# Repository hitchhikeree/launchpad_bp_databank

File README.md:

DataBank LaunchPad BoosterPack
=========================

A dual SD card and SPI Flash board for logging tons of data or accessing a bunch of it.

## Project Links
- <a href="http://www.hitchhikeree.org/databank/">HitchhikerEE page</a>
- <a href="http://youtu.be/DQmhQuYcrzk">YouTube video</a>
- <a href="https://docs.google.com/folder/d/0B5HjtPsFD8u5alU0WkpRbFBrZk0/edit?usp=sharing">Design files on Google Drive</a>
- <a href="http://e2e.ti.com/group/microcontrollerprojects/m/boosterpackcontest/664831.aspx">LaunchPad BoosterPack Contest page</a>

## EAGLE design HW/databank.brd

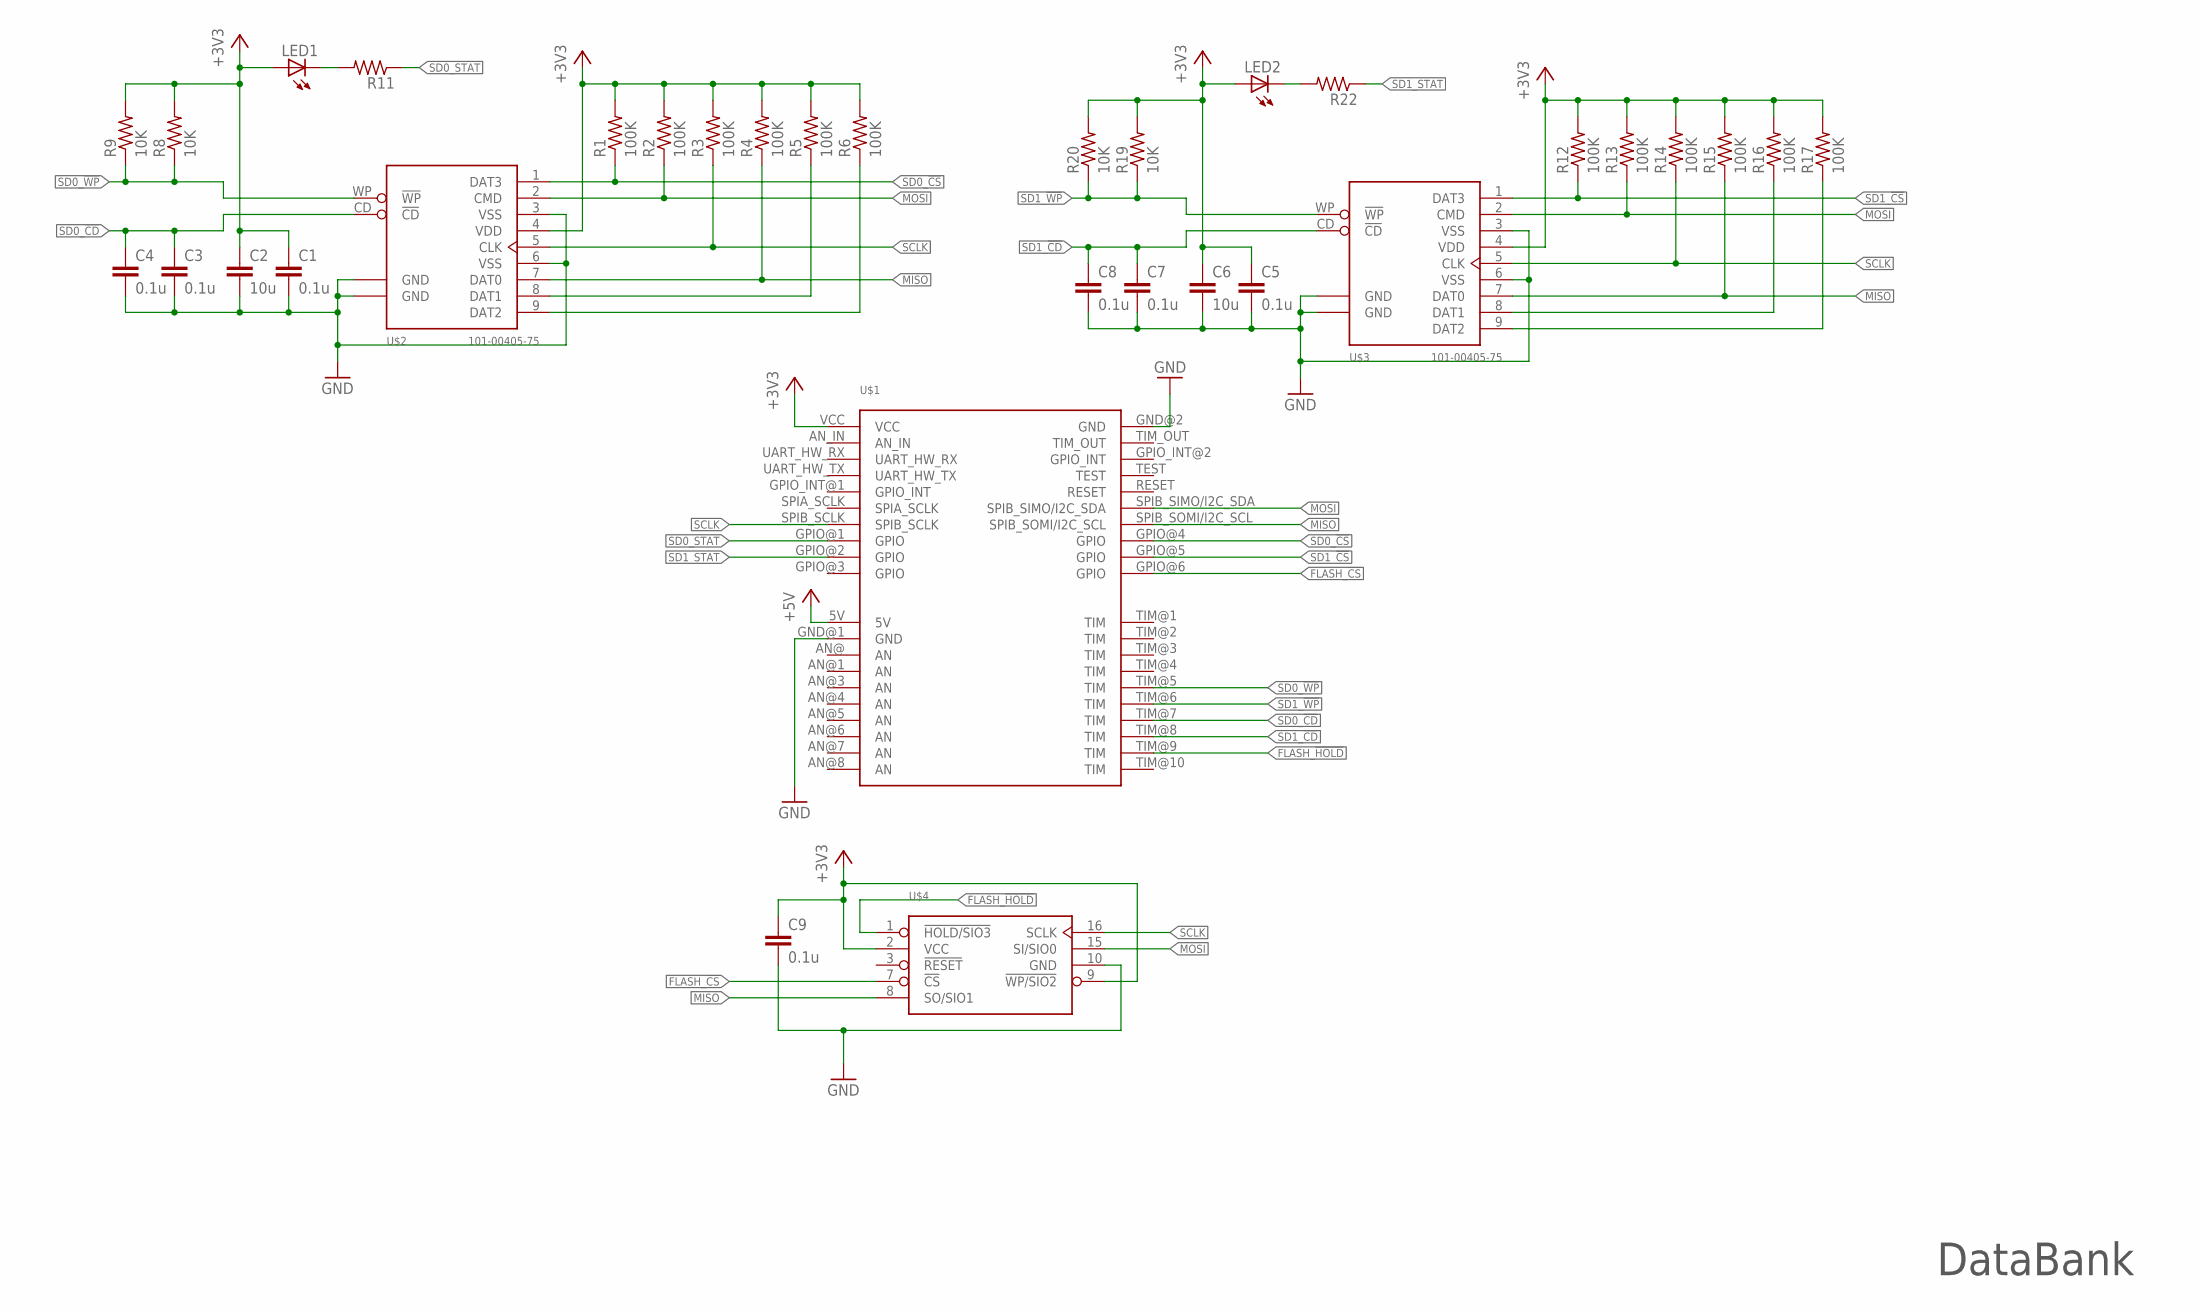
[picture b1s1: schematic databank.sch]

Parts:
C1, C3, C4, C5, C7, C8, C9: 0.1u; C0603
C2, C6: 10u; C0603
LED1, LED2: LEDCHIP-LED0603; CHIP-LED0603
R1, R2, R3, R4, R5, R6, R12, R13, R14, R15, R16, R17: 100K; R0603
R8, R9, R19, R20: 10K; R0603
R11, R22: R-US_R0603; R0603
U$1: LAUNCHPAD_BOOSTER_PACK
U$2, U$3: 101-00405-75
U$4: MX25L25635E; SO-16LD

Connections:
+3V3: C1.1, C2.1, C5.1, C6.1, C9.1, LED1.A, LED2.A, R1.2, R2.2, R3.2, R4.2, R5.2, R6.2, R8.2, R9.2, R12.2, R13.2, R14.2, R15.2, R16.2, R17.2, R19.2, R20.2, U$1.VCC, U$2.4 (VDD), U$3.4 (VDD), U$4.2 (VCC), U$4.9 (!WP/SIO2)
+5V: U$1.5V
FLASH_!CS: U$1.GPIO@6 (GPIO), U$4.7 (!CS)
FLASH_!HOLD: U$1.TIM@9 (TIM), U$4.1 (!HOLD/SIO3)
GND: C1.2, C2.2, C3.2, C4.2, C5.2, C6.2, C7.2, C8.2, C9.2, U$1.GND@1 (GND), U$1.GND@2 (GND), U$2.3 (VSS), U$2.6 (VSS), U$2.G1$GND (GND), U$2.G2$GND (GND), U$3.3 (VSS), U$3.6 (VSS), U$3.G1$GND (GND), U$3.G2$GND (GND), U$4.10 (GND)
MISO: R4.1, R15.1, U$1.SPIB_SOMI/I2C_SCL, U$2.7 (DAT0), U$3.7 (DAT0), U$4.8 (SO/SIO1)
MOSI: R2.1, R13.1, U$1.SPIB_SIMO/I2C_SDA, U$2.2 (CMD), U$3.2 (CMD), U$4.15 (SI/SIO0)
unnamed: LED1.C, R11.2
unnamed: R16.1, U$3.8 (DAT1)
unnamed: R17.1, U$3.9 (DAT2)
unnamed: R5.1, U$2.8 (DAT1)
unnamed: R6.1, U$2.9 (DAT2)
unnamed: LED2.C, R22.2
SCLK: R3.1, R14.1, U$1.SPIB_SCLK, U$2.5 (CLK), U$3.5 (CLK), U$4.16 (SCLK)
SD0_!CD: C3.1, C4.1, U$1.TIM@7 (TIM), U$2.CD (!CD)
SD0_!CS: R1.1, U$1.GPIO@4 (GPIO), U$2.1 (DAT3)
SD0_!WP: R8.1, R9.1, U$1.TIM@5 (TIM), U$2.WP (!WP)
SD0_STAT: R11.1, U$1.GPIO@1 (GPIO)
SD1_!CD: C7.1, C8.1, U$1.TIM@8 (TIM), U$3.CD (!CD)
SD1_!CS: R12.1, U$1.GPIO@5 (GPIO), U$3.1 (DAT3)
SD1_!WP: R19.1, R20.1, U$1.TIM@6 (TIM), U$3.WP (!WP)
SD1_STAT: R22.1, U$1.GPIO@2 (GPIO)

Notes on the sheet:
DataBank

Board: 2 copper layers, 33 parts (0 on the bottom side), 21 nets, no tracks yet.

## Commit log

2013-02-24 Adding base CAD files
2013-03-02 Finished design
